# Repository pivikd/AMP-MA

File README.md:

# Project Status

   >AMP-MA is currently in the pre-release development phase and is considered unstable. The project is at the stage of creating the first prototype. The first stable release is scheduled for December 2026.

# AMP-MA (AMP Modus Aequale)

AMP-MA (standing for Modus Aequale, signifying a rhythmic, ideal tone and modular structure) is an open-source, transistor-based guitar combo amplifier project. It is designed to bridge the gap between solid-state reliability and the organic, harmonic richness of vacuum tube sound.

The project focuses on a modular architecture, originally developed as a high-fidelity upgrade for the **Epiphone 15C** PCB. By utilizing independent blocks, AMP-MA allows for seamless customization and easier adaptation to various amp enclosures.

This project is designed and maintained by: [Danylo Pyvovarov](https://github.com/pivikd).

> Detailed description about project in the Datasheet [-->](#documentation)

   1. [Key Features](#key-features)
   1. [Signal Chain](#signal-chain)
   1. [Integrated Tone Stacks](#integrated-tone-stacks)
   1. [Controls and Connectors](#controls-and-connectors)
   1. [Transistor Notes](#transistor-notes)
   1. [Power Supply](#power-supply)
   1. [Safety](#safety)
   1. [Documentation](#documentation)
   1. [License](#license)
   1. [Credits](#credits)
<!-- 1. [Integrated Effects Modules](#integrated-effects-modules) -->

## Key Features
   - **Tube-like Architecture**: Uses a **Fetzer Valve** based stage with a **2SK30A** JFET to achieve a warm, organic sound and harmonic saturation that mimics vacuum tube behavior.

   - **Dual Input Support**: Designed to handle two guitars simultaneously.

   - **Legendary Tone Stacks**: Features a 3-band EQ based on the classic tone stacks ([Integrated Tone Stacks](#integrated-tone-stacks)).

   - **Integrated Compression**: Built-in compressor block based on the vintage **Ibanez CP835** circuitry.

   - **Modular Tone Stacks**: One board supports three tone stack topologies and five voicings, selected with solder jumpers and component values, so the tone can be changed without redesigning the board.

## Signal Chain
   1. Input buffer
   1. Compressor
   1. Bypass
   1. Preamp
   1. Tone Stack
   1. Amp

<!-- ## Integrated Effects Modules
|       Effect      |   based on   |  Status  |
|-------------------|--------------|---------|
| Compressor        | Ibanez CP835 |  done   |
| Over Drive        | Boss OD3     | planned  |
| Chorus            | Boss Ch1     | planned  | -->

## Integrated Tone Stacks

One board supports three topologies and five voicings. The voicing is selected with solder jumpers and component values.

| Voicing | Values |
|---------|--------|
| Fender Treble-Middle-Bass | original |
| Marshall (JCM900 2100 SL-X) | original |
| Dumble Rock | original |
| **TS-0** (based on Marshall JCM900 2100 SL-X) | own, calculated for real component values |
| **TS-1** (based on Dumble Rock) | own, calculated for real component values |

   - **Fender, Marshall and Dumble Rock** use the original values of the classic circuits.
   - **TS-0 and TS-1** are my own variants: the values are recalculated to sound like the originals while using real, available components.

The exact component values, jumper settings and frequency-response plots are given in the datasheet (see [Documentation](#documentation)), which is still being written.

## Controls and Connectors
   - **Front panel:**
      - 2 inputs (with a volume control for each);
      - tone stack: Bass, Middle, Treble;
      - compressor with Sustain control and a bypass switch with an LED indicator.
   - **Rear panel:**
      - power switch;
      - output for an external speaker.

## Transistor Notes

The circuit uses **2SK30A** JFETs, and their parameters (pinch-off voltage **Vp** and drain current **Idss**) vary widely from device to device. The bias components of the Fetzer Valve stage depend on the specific transistor, so measure Vp and Idss of your own part and calculate the values.

Example for a 2SK30A with the measured values:

| Parameter | Value |
|-----------|-------|
| Vp | 2.2 V |
| Idss | 3.8 mA |
| Vcc | 15 V |
| **Rs** | 481 Ω |
| **Rd** | 2511 Ω |
| **Cp** | 331.2 nF |
| **Av** (gain) | 8.3 dB |

>More details will be given in the datasheet. [-->](#documentation)

## Power Supply
   - Mains transformer module **PXB-10C**, 2 × 14 V AC;
   - fuse **F1** – 250 mA;
   - bridge rectifier (D1–D4);
   - **LM317 / LM337** regulators, approximately ±15 V.

>More details will be given in the datasheet. [-->](#documentation)

## Safety

> [!WARNING]
> The amplifier is powered from the **mains voltage**. Mains voltage is dangerous and can be lethal.
> Build, test and power up the device only if you know how to work with mains-powered equipment.
> Always use the fuse, keep the mains part insulated and enclosed, and disconnect the device from the mains before touching the board.
> The project is an unstable prototype and is provided **without any warranty**. You build and use it at your own risk.

# Other
## Documentation

The datasheet matches the hardware revision in this repository. It is up to date, but **not yet complete**: some sections (for example BOM, PCB layout, build notes, testing, revision history) may still be unfinished, and some specifications may be marked TBD.

   - [Datasheet (PDF)](AMP_MA.pdf)

## License

Schematics, PCB layout, and all source files and documentation are licensed under
[CERN-OHL-S-2.0](LICENSE). Copyright (c) 2026 Pyvovarov Danylo.

   ### Exceptions

   The following artwork elements are **not covered by CERN-OHL-S-2.0** and are not
   licensed under it. They are included solely as cultural references to 1990s and
   2000s rock music design:

   - the snake silhouette from Metallica Black album;
   - the winged figure silhouette from Linkin Park Hybrid Theory album;
<!--   - the "AC/DC" lettering with the lightning bolt. -->

   All rights to these images and names remain with their respective rights holders.
   They are not part of the open-source license and may not be reused without
   permission from the rights holder.
# Credits

   - Compressor: **Ibanez CP835** - [schematic](https://www.scribd.com/document/976348354/Ibanez-CP835-Schematic)
   - Preamp: **Fetzer Valve** - [Runoff Groove](https://www.runoffgroove.com/fetzervalve.html)
   - Tone stack: **Marshall JCM900 2100 SL-X** - [Stompbox Electronics, "The Marshall Tone Stacks"](https://stompboxelectronics.com/2023/12/16/the-marshall-tone-stacks/)
   - Power amplifier: **LM1875** - [Texas Instruments datasheet](https://www.ti.com/lit/ds/symlink/lm1875.pdf)
   - Tone stack: **Fender TMB** and **Dumble Rock** - [Yet Another Tonestack Calculator](https://tonestack.yuriturov.com/)
   - **Epiphone 15C** – the amplifier whose PCB this project was originally designed to upgrade

   All product names and trademarks (Ibanez, Fender, Marshall, Dumble, Epiphone, Metallica, Linkin Park, AC/DC) belong to their respective owners.
   This project is not affiliated with or endorsed by them.

#
>Handcrafted by human. AI was used to help format and write the text of this README and the datasheet.

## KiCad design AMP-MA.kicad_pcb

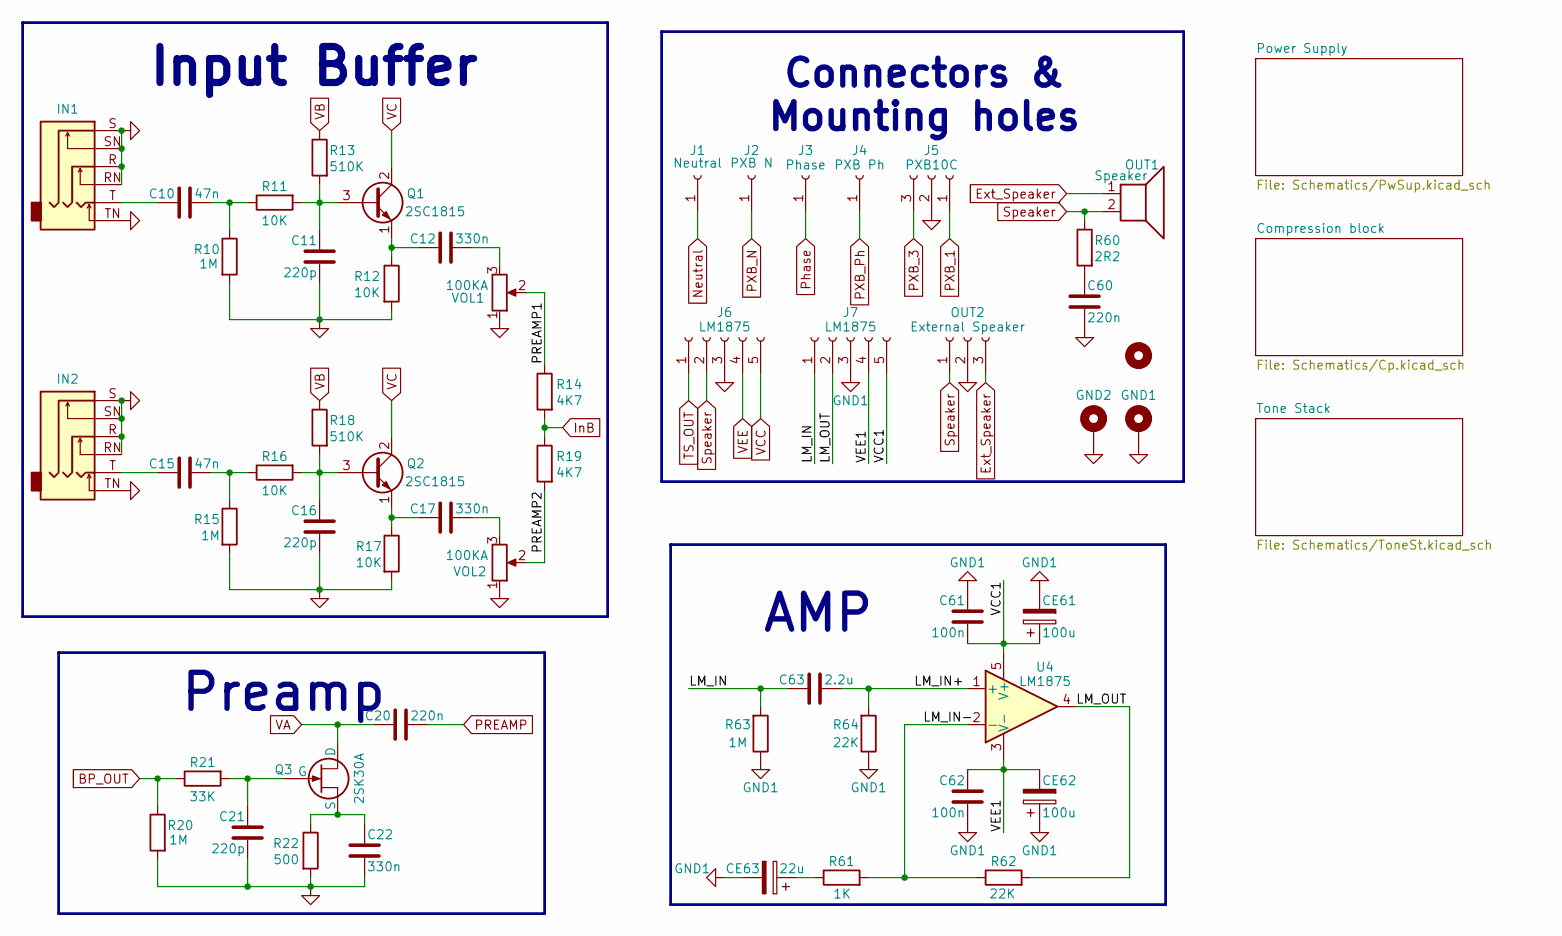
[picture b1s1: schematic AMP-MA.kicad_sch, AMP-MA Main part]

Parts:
C10, C15: 47n; C_disc_D7_W2.5_P5
C11, C16, C21: 220p; C_disc_D7_W2.5_P5
C12, C17, C22: 330n; C_disc_D7_W2.5_P5
C20, C60: 220n; C_disc_D7_W2.5_P5
C61, C62: 100n; C_disc_D7_W2.5_P5
C63: 2.2u; C_disc_D7_W2.5_P5
CE61, CE62: 100u; CP_Radial_D6.3mm_P2.50mm
CE63: 22u; CP_Radial_D5.0mm_P2.50mm
GND1: MountingHole_Pad; MountingHole_2.2mm_M2_DIN965_Pad
GND2: MountingHole_Pad; MountingHole_2.2mm_M2_Pad_Via
H2: MountingHole; MountingHole_2.2mm_M2
IN1, IN2: Jack_3_6pin
J1: Neutral; connector
J2: PXB N; connector
J3: Phase
J4: PXB Ph
J5: PXB10C; JST_XH_B3B-XH-A_1x03_P2.50mm_Vertical
J6, J7: LM1875; JST_XH_B5B-XH-A_1x05_P2.50mm_Vertical
OUT1: Speaker; PinSocket_1x02_P2.54mm_Vertical
OUT2: External Speaker; JST_XH_B3B-XH-A_1x03_P2.50mm_Vertical
Q1, Q2: 2SC1815; TO-92_Inline_Wide
Q3: 2SK30A; TO-92_Inline_Wide
R10, R15, R20, R63: 1M; R_Axial_DIN0207_L6.3mm_D2.5mm_P10.16mm_Horizontal
R11, R12, R16, R17: 10K; R_Axial_DIN0207_L6.3mm_D2.5mm_P10.16mm_Horizontal
R13, R18: 510K; R_Axial_DIN0207_L6.3mm_D2.5mm_P10.16mm_Horizontal
R14, R19: 4K7; R_Axial_DIN0207_L6.3mm_D2.5mm_P10.16mm_Horizontal
R21: 33K; R_Axial_DIN0207_L6.3mm_D2.5mm_P10.16mm_Horizontal
R22: 500; R_Axial_DIN0207_L6.3mm_D2.5mm_P10.16mm_Horizontal
R60: 2R2; R_Axial_DIN0207_L6.3mm_D2.5mm_P10.16mm_Horizontal
R61: 1K; R_Axial_DIN0207_L6.3mm_D2.5mm_P10.16mm_Horizontal
R62, R64: 22K; R_Axial_DIN0207_L6.3mm_D2.5mm_P10.16mm_Horizontal
U4: LM1875; TO-220-5_P3.4x3.7mm_StaggerOdd_Lead3.8mm_Vertical
VOL1, VOL2: 100KA; potentiometer

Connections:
/LM_IN: C63.1, J7.1, R63.2
/LM_IN+: C63.2, R64.2, U4.1 (+)
/LM_IN-: R61.2, R62.1, U4.2 (-)
/LM_OUT: J7.2, R62.2, U4.4
/PREAMP1: R14.1, VOL1.2
/PREAMP2: R19.2, VOL2.2
/VCC1: C61.2, CE61.1, J7.5, U4.5 (V+)
/VEE1: C62.1, CE62.2, J7.4, U4.3 (V-)
BP_OUT: R20.1, R21.1; also elsewhere on the board
Ext_Speaker: OUT1.1, OUT2.3
GND: C11.1, C16.1, C21.1, C22.1, C60.2, GND1.1 (1_1), GND2.1 (1_1), IN1.R, IN1.RN, IN1.S, IN1.SN, IN1.TN, IN2.R, IN2.RN, IN2.S, IN2.SN, IN2.TN, J5.2, J6.3, OUT2.2, R10.2, R12.2, R15.2, R17.2, R20.2, R22.2, VOL1.1, VOL2.1; also elsewhere on the board
GND1: C61.1, C62.2, CE61.2, CE62.1, CE63.2, J7.3, R63.1, R64.1
InB: R14.2, R19.1; also elsewhere on the board
unnamed: C10.1, IN1.T
unnamed: C10.2, R10.1, R11.1
unnamed: C12.2, VOL1.3
unnamed: C15.1, IN2.T
unnamed: C15.2, R15.1, R16.1
unnamed: C17.2, VOL2.3
unnamed: C60.1, R60.2
unnamed: CE63.1, R61.1
unnamed: C11.2, Q1.3 (B), R11.2, R13.2
unnamed: C12.1, Q1.1 (E), R12.1
unnamed: C16.2, Q2.3 (B), R16.2, R18.2
unnamed: C17.1, Q2.1 (E), R17.1
unnamed: C21.2, Q3.2 (G), R21.2
unnamed: C22.2, Q3.3 (S), R22.1
Neutral: J1.1 (Pin_1_1); also elsewhere on the board
PREAMP: C20.2; also elsewhere on the board
PXB_1: J5.1; also elsewhere on the board
PXB_3: J5.3; also elsewhere on the board
PXB_N: J2.1 (Pin_1_1); also elsewhere on the board
Speaker: J6.2, OUT1.2, OUT2.1, R60.1
TS_OUT: J6.1; also elsewhere on the board
VA: C20.1, Q3.1 (D); also elsewhere on the board
VB: R13.1, R18.1; also elsewhere on the board
VC: Q1.2 (C), Q2.2 (C); also elsewhere on the board
VCC: J6.5; also elsewhere on the board
VEE: J6.4; also elsewhere on the board

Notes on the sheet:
Preamp
Connectors & Mounting holes
AMP
Input Buffer

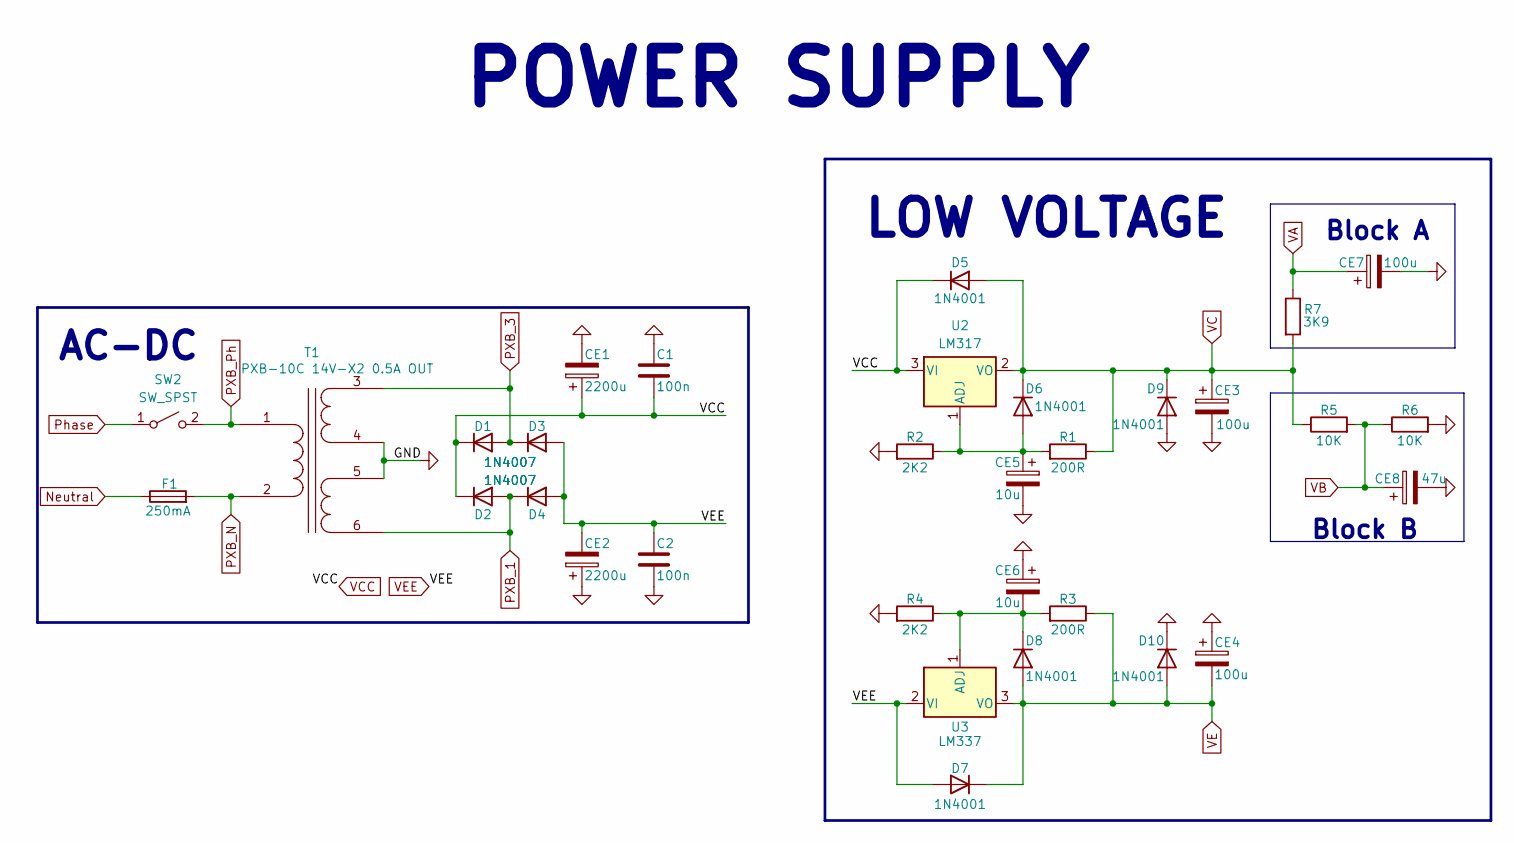
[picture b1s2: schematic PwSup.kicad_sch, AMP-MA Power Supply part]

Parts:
C1, C2: 100n; C_disc_D7_W2.5_P5
CE1, CE2: 2200u; CP_Radial_D16.0mm_P7.50mm
CE3, CE4, CE7: 100u; CP_Radial_D6.3mm_P2.50mm
CE5, CE6: 10u; CP_Radial_D5.0mm_P2.50mm
CE8: 47u; CP_Radial_D5.0mm_P2.50mm
D1, D2, D3, D4: 1N4007; D_DO-41_SOD81_P10.16mm_Horizontal
D5, D6, D7, D8, D9, D10: 1N4001; D_DO-41_SOD81_P10.16mm_Horizontal
F1: 250mA; Fuseholder_Clip-5x20mm_Littelfuse_520_Inline_P20.50x5.80mm_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
R1, R3: 200R; R_Axial_DIN0207_L6.3mm_D2.5mm_P10.16mm_Horizontal
R2, R4: 2K2; R_Axial_DIN0207_L6.3mm_D2.5mm_P10.16mm_Horizontal
R5, R6: 10K; R_Axial_DIN0207_L6.3mm_D2.5mm_P10.16mm_Horizontal
R7: 3K9; R_Axial_DIN0207_L6.3mm_D2.5mm_P10.16mm_Horizontal
SW2: SW_SPST
T1: PXB-10C 14V-X2 0.5A OUT
U2: LM317; TO-220-3_Horizontal_TabDown
U3: LM337; TO-220-3_Horizontal_TabDown

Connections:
GND: C1.2, C2.2, CE1.2, CE2.1, CE3.2, CE4.1, CE5.2, CE6.1, CE7.2, CE8.2, D9.2 (A), D10.1 (K), R2.2, R4.2, R6.2, T1.4 (SB), T1.5 (SC); also elsewhere on the board
unnamed: CE5.1, D6.2 (A), R1.2, R2.1, U2.1 (ADJ)
unnamed: CE6.2, D8.1 (K), R3.2, R4.1, U3.1 (ADJ)
unnamed: SW2.2 (B), T1.1 (AA)
Neutral: F1.1; also elsewhere on the board
PXB_1: D2.2 (A), D4.1 (K), T1.6 (SD); also elsewhere on the board
PXB_3: D1.2 (A), D3.1 (K), T1.3 (SA); also elsewhere on the board
PXB_N: F1.2, T1.2 (AB); also elsewhere on the board
VA: CE7.1, R7.1; also elsewhere on the board
VB: CE8.1, R5.2, R6.1; also elsewhere on the board
VC: CE3.1, D5.2 (A), D6.1 (K), D9.1 (K), R1.1, R5.1, R7.2, U2.2 (VO); also elsewhere on the board
VCC: C1.1, CE1.1, D1.1 (K), D2.1 (K), D5.1 (K), U2.3 (VI); also elsewhere on the board
VE: CE4.2, D7.1 (K), D8.2 (A), D10.2 (A), R3.1, U3.3 (VO); also elsewhere on the board
VEE: C2.1, CE2.2, D3.2 (A), D4.2 (A), D7.2 (A), U3.2 (VI); also elsewhere on the board

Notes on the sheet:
AC-DC
Block A
Block B
LOW VOLTAGE
POWER SUPPLY

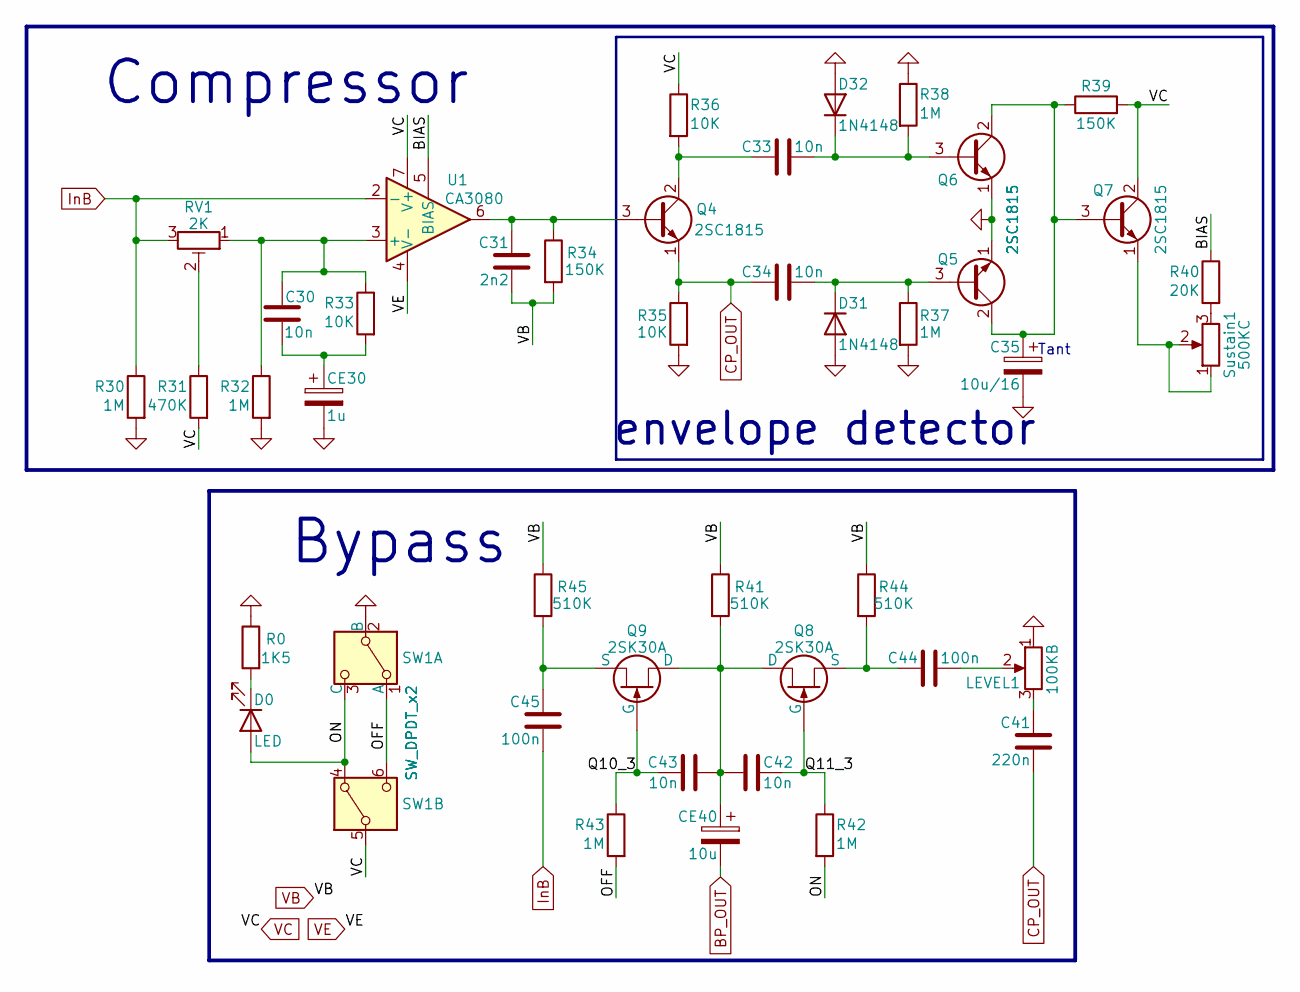
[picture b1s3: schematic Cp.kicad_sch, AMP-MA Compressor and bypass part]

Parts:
C30: 10n; C_disc_D7_W2.5_P5
C31: 2n2; C_Disc_D4.3_W1.9_P5.00
C33, C34, C42, C43: 10n; C_Disc_D4.3_W1.9_P5.00
C35: 10u/16; CP_Radial_Tantal_D5.5mm_P2.50mm
C41: 220n; C_disc_D7_W2.5_P5
C44, C45: 100n; C_disc_D7_W2.5_P5
CE30: 1u; CP_Radial_D4.0mm_P2.00mm
CE40: 10u; CP_Radial_D5.0mm_P2.50mm
D0: LED; LED_D3.0mm_Horizontal_O6.35mm_Z6.0mm
D31, D32: 1N4148; D_DO-35_SOD27_P7.62mm_Horizontal
LEVEL1: 100KB; Potentiometer_Bourns_3296W_Vertical
Q4, Q5, Q6, Q7: 2SC1815; TO-92_Inline_Wide
Q8, Q9: 2SK30A; TO-92_Inline_Wide
R0: 1K5; R_Axial_DIN0207_L6.3mm_D2.5mm_P10.16mm_Horizontal
R30, R32, R37, R38, R42, R43: 1M; R_Axial_DIN0207_L6.3mm_D2.5mm_P10.16mm_Horizontal
R31: 470K; R_Axial_DIN0207_L6.3mm_D2.5mm_P10.16mm_Horizontal
R33, R35, R36: 10K; R_Axial_DIN0207_L6.3mm_D2.5mm_P10.16mm_Horizontal
R34, R39: 150K; R_Axial_DIN0207_L6.3mm_D2.5mm_P10.16mm_Horizontal
R40: 20K; R_Axial_DIN0207_L6.3mm_D2.5mm_P10.16mm_Horizontal
R41, R44, R45: 510K; R_Axial_DIN0207_L6.3mm_D2.5mm_P10.16mm_Horizontal
RV1: 2K; Potentiometer_Bourns_3296W_Vertical
SW1: SW_DPDT_x2; SW DPDT
Sustain1: 500KC; potentiometer
U1: CA3080; DIP-8_W7.62mm

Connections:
/Compression block/BIAS: R40.1, U1.5 (BIAS)
/Compression block/OFF: R43.2, SW1.1 (A), SW1.6 (C)
/Compression block/ON: D0.2 (A), R42.2, SW1.3 (C), SW1.4 (A)
/Compression block/Q10_3: C43.2, Q9.2 (G), R43.1
/Compression block/Q11_3: C42.1, Q8.2 (G), R42.1
BP_OUT: CE40.2; also elsewhere on the board
CP_OUT: C34.1, C41.1, Q4.1 (E), R35.1
GND: C35.2, CE30.2, D31.2 (A), D32.2 (A), LEVEL1.1, Q5.1 (E), Q6.1 (E), R0.1, R30.2, R32.2, R35.2, R37.2, R38.1, SW1.2 (B); also elsewhere on the board
InB: C45.1, R30.1, RV1.3, U1.2 (-); also elsewhere on the board
unnamed: C30.2, CE30.1, R33.2
unnamed: C41.2, LEVEL1.3
unnamed: C44.2, LEVEL1.2
unnamed: D0.1 (K), R0.2
unnamed: C34.2, D31.1 (K), Q5.3 (B), R37.1
unnamed: C33.2, D32.1 (K), Q6.3 (B), R38.2
unnamed: C31.1, Q4.3 (B), R34.1, U1.6
unnamed: C33.1, Q4.2 (C), R36.2
unnamed: C35.1, Q5.2 (C), Q6.2 (C), Q7.3 (B), R39.1
unnamed: Q7.1 (E), Sustain1.1, Sustain1.2
unnamed: C42.2, C43.1, CE40.1, Q8.1 (D), Q9.1 (D), R41.2
unnamed: C44.1, Q8.3 (S), R44.2
unnamed: C45.2, Q9.3 (S), R45.2
unnamed: R31.1, RV1.2
unnamed: R40.2, Sustain1.3
unnamed: C30.1, R32.1, R33.1, RV1.1, U1.3 (+)
VB: C31.2, R34.2, R41.1, R44.1, R45.1; also elsewhere on the board
VC: Q7.2 (C), R31.2, R36.1, R39.2, SW1.5 (B), U1.7 (V+); also elsewhere on the board
VE: U1.4 (V-); also elsewhere on the board

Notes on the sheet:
Bypass
envelope detector
Tant
Compressor

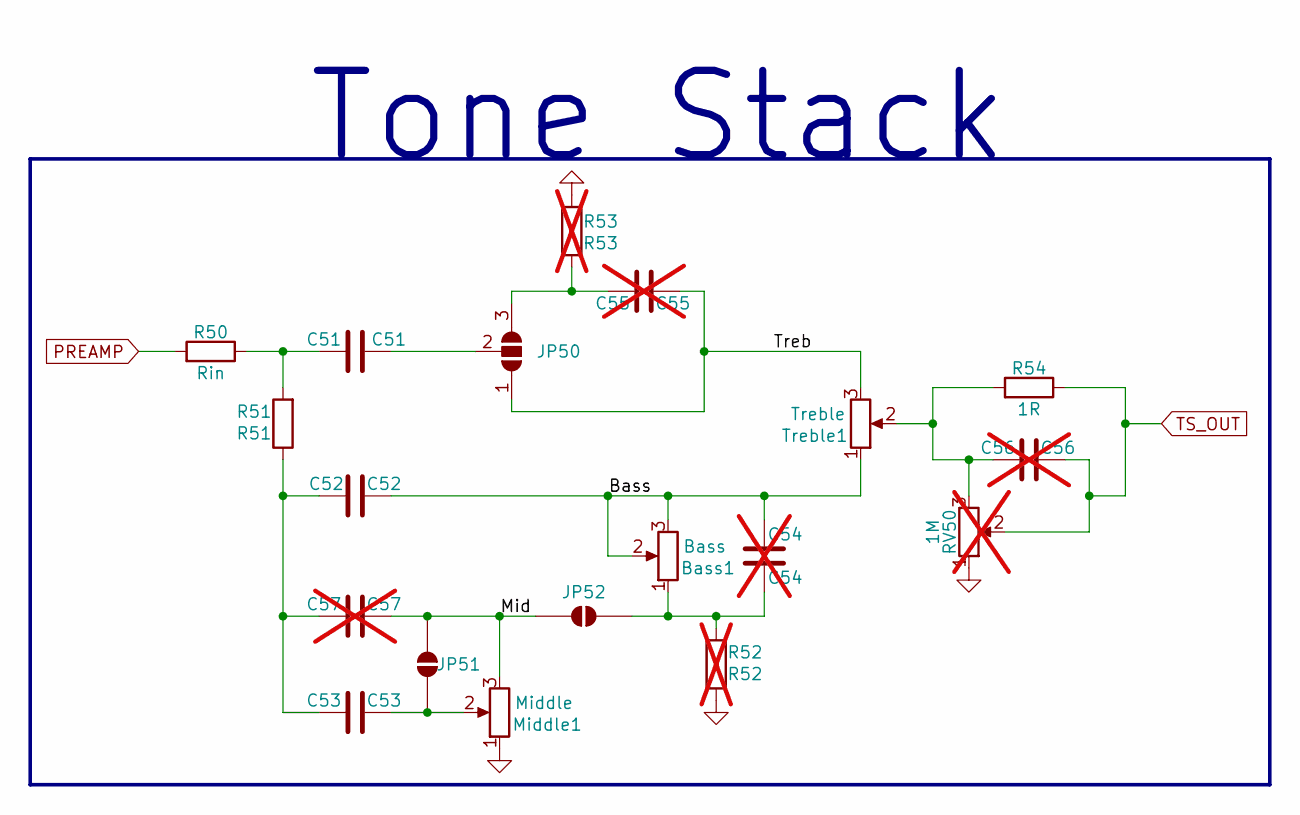
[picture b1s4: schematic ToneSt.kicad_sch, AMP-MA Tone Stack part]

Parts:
Bass1: Bass; potentiometer
C51: C51; C_disc_D7_W2.5_P5
C52: C52; C_disc_D7_W2.5_P5
C53: C53; C_disc_D7_W2.5_P5
C54: C54; C_disc_D7_W2.5_P5; not fitted
C55: C55; C_disc_D7_W2.5_P5; not fitted
C56: C56; C_disc_D7_W2.5_P5; not fitted
C57: C57; C_disc_D7_W2.5_P5; not fitted
JP50: SolderJumper_3_Open; SolderJumper-3_P2.0mm_Open_TrianglePad1.0x1.5mm_NumberLabels
JP51, JP52: SolderJumper_2_Open; SolderJumper-2_P1.3mm_Open_TrianglePad1.0x1.5mm
Middle1: Middle; potentiometer
R50: Rin; R_Axial_DIN0207_L6.3mm_D2.5mm_P10.16mm_Horizontal
R51: R51; R_Axial_DIN0207_L6.3mm_D2.5mm_P10.16mm_Horizontal
R52: R52; R_Axial_DIN0207_L6.3mm_D2.5mm_P10.16mm_Horizontal; not fitted
R53: R53; R_Axial_DIN0207_L6.3mm_D2.5mm_P10.16mm_Horizontal; not fitted
R54: 1R; R_Axial_DIN0207_L6.3mm_D2.5mm_P10.16mm_Horizontal
RV50: 1M; Potentiometer_Bourns_3296W_Vertical; not fitted
Treble1: Treble; potentiometer

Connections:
/Tone Stack/Bass: Bass1.2, Bass1.3, C52.2, C54.2, Treble1.1
/Tone Stack/Mid: C57.2, JP51.1 (A), JP52.1 (A), Middle1.3
/Tone Stack/Treb: C55.2, JP50.1 (A), Treble1.3
GND: Middle1.1, R52.1, R53.1, RV50.1; also elsewhere on the board
unnamed: C51.1, R50.1, R51.2
unnamed: C52.1, C53.1, C57.1, R51.1
unnamed: C56.1, R54.2, RV50.3, Treble1.2
unnamed: C55.1, JP50.3 (B), R53.2
unnamed: C51.2, JP50.2 (C)
unnamed: C53.2, JP51.2 (B), Middle1.2
unnamed: Bass1.1, C54.1, JP52.2 (B), R52.2
PREAMP: R50.2; also elsewhere on the board
TS_OUT: C56.2, R54.1, RV50.2; also elsewhere on the board

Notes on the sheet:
Tone Stack

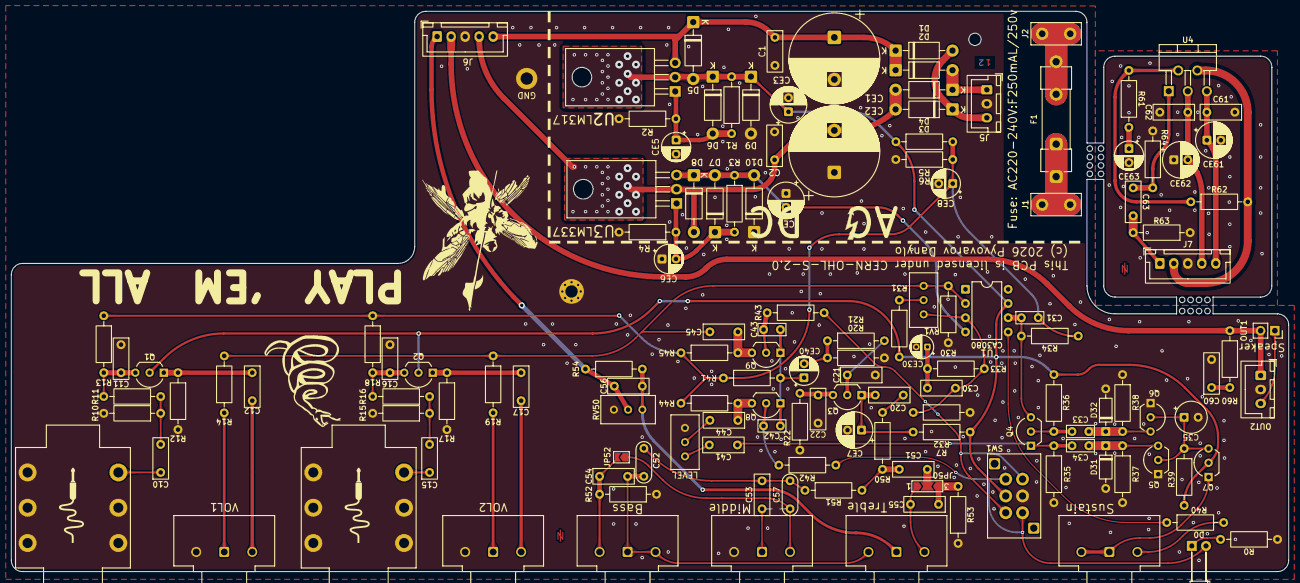
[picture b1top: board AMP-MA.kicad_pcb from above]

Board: 2 copper layers, 228.0 x 100.0 mm, 144 parts (1 on the bottom side), 74 nets.

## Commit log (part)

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2026-04-23 Init commit
2026-04-23 Schem upd
    added Copressor module
2026-04-24 Schem upd
    added Voltage supply
2026-04-25 added own library
2026-04-26 Schem & lib upd
    added audiojack symbol & added PREAMP cascade
2026-04-27 ReadME upd
2026-04-27 Project renamed
2026-04-28 Schem & Lib upd
    Lib: added footprint and Symbol foe new 6pin jack Schem: changed jacks
2026-04-29 Schem upd
    Tone Stack addded
2026-04-30 Schem & README upd
    added AMP block
2026-05-02 power supply upd
    9v pover supply changed on AC-DC tancformer
2026-05-03 Big upd
    moved hierarical Sheets to direсtory Schematics, revorked power supply
2026-05-03 footprints assigned
2026-05-04 directory cleared, Schem upd
    The input mixer changed from passive to active(TL072)
2026-05-05 Schem upd
    in bypass button changed on SPDT switch
2026-05-06 Schem upd
    The LED is powered by the low voltage supply, not by the effect
2026-05-06 Schem upd
    Managed power supply for TL072
2026-05-07 Schem upd & added .gitignore
2026-05-11 Lib & Schematic upd
    Jack connector symbol update. Made basic layout has been made
2026-05-18 smal schem upd

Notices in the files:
AMP-MA.kicad_pcb:
License: CERN-OHL-S-2.0
This PCB is licensed under CERN-OHL-S-2.0
AMP-MA.kicad_sch:
Copyright (c) 2026 Pyvovarov Dannylo
